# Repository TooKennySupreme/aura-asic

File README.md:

aura-asic
=========

## **Aura ASIC universal PCB | Created by the Community**

This project originated from the works of Jasinlee, and his universal PCB for most current and upcoming ASIC designs.

To see where this project started of from, please follow this link:- [Roots](https://litecointalk.org/index.php?topic=12567.0)

If you are waiting for the release of a scrypt ASIC, follow Jasinlee's project on [Litecointalk.org](https://litecointalk.org/index.php?topic=2702.0)

### To do list:
  - Convert board from Kicad to Altium
  - Convert board from Kicad to Eagle
  - TBUpdateded

### Current Issues:
  - item will be updated

### Contributors:

_jasinlee_:
LTCasicYDKQVGySmG5vwCiqiZFpMcr7oMi

_losh11_:
LfVszG74eZKRxrx2s29rQs3MR2Vvau3LsE

_smartbitcoin_: TBUpdateded

_artilectinc.com_: TBUpdateded

_Cheshyr_:
1CheshyrZsZ5X1XWW5EQUhGTExx6LTQBw4

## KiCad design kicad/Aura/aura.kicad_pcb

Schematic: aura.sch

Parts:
C1: 50p
C2, C23, C24, C25, C26: 22n
C3: 1.2n
C4: 1p
C5: .22u
C6: .1u
C7, C14, C15: 330u
C8, C9, C10, C11: 330n
C12: 10u
C13, C16, C17, C18, C19, C32, C33, C34, C35, C39, C40, C41, C42, C43, C44, C45, C46, C47, C48, C49, C50, C51, C52, C53, C54, C55, C56, C57, C58, C59, C60, C61, C62, C63, C64, C65, C66, C67, C68, C69, C70, C71, C72, C73, C74, C75, C76, C77, C78, C79, C80, C81, C82, C83, C84, C85, C86, C87, C88, C89, C90, C91, C92, C93, C94, C103, C104, C105, C106, C107, C108, C109, C110, C111, C112, C113, C114, C115, C116, C117, C118, C119, C120, C121, C122, C123, C124, C125, C126, C127, C128, C129, C130, C131, C132, C133, C134, C135, C136, C137, C138, C139, C140, C141, C142, C143, C144, C145, C146, C147, C148, C149, C150, C151, C152, C153, C154, C155, C156, C157, C158, C159, C160, C161, C162, C171, C172, C173, C174, C175, C176, C177, C178, C179, C180, C181, C182, C183, C184, C185, C186, C187, C188, C189, C190, C191, C192, C193, C194, C195, C196, C197, C198, C199, C200, C201, C202, C203, C204, C205, C206, C207, C208, C209, C210, C211, C212, C213, C214, C215, C216, C217, C218, C219, C220, C221, C222, C223, C224, C225, C226, C227, C228, C229, C230, C239, C240, C241, C242, C243, C244, C245, C246, C247, C248, C249, C250, C251, C252, C253, C254, C255, C256, C257, C258, C259, C260, C261, C262, C263, C264, C265, C266, C267, C268, C269, C270, C271, C272, C273, C274, C275, C276, C277, C278, C279, C280, C281, C282, C283, C284, C285, C286, C287, C288, C289, C290, C291, C292, C293, C294, C295, C296, C297, C298: 1u
C20: 10n
C21: 10nf
C22: 560u
C27, C28, C29, C30, C95, C96, C97, C98, C163, C164, C165, C166, C231, C232, C233, C234: 0.47u
C31, C36, C37, C38, C99, C100, C101, C102, C167, C168, C169, C170, C235, C236, C237, C238, C299: 0.1u
D1: VRRM = 45V
FB1, FB2, FB3: 120R
J1: PCIE_PWR
J2: USB
J3: DIL8
J4: DIL6
JP1, JP2, JP3, JP4: JUMPER
L1: 2.2u
L2, L3, L4, L5: 600n
Q1: FDG1024NZ; SC70-6
Q2, Q3, Q4, Q5, Q6, Q7, Q8, Q9: MOS_N
R1: 22k
R2: 19.1k
R3, R4, R5, R6, R9, R11, R17, R18, R32, R33, R34, R35, R36, R37, R38, R39, R44, R45, R46, R47, R48, R49, R50, R51, R56, R57, R58, R59, R60, R61, R62, R63, R68, R69, R70, R71, R72, R73, R74, R75: 1k
R7: 1G
R8: 100k
R10: 88k
R12: 11k
R13, R14, R15, R16: 8.4k
R19, R20, R26, R27, R28, R30, R41, R43, R53, R55, R65, R67: 10k
R21: 402
R22, R23, R24, R25: 27.3k
R29, R31, R40, R42, R52, R54, R64, R66: 5.6k
RP1: 10k
TH1: 6.8k RT
TH2, TH3: 2.2k RT
TP1, TP2, TP3, TP4, TP5, TP6, TP7, TP8, TP9, TP10, TP11, TP12, TP13, TP14, TP15: TST
U1: ISL6306
U2: PCF8574_SO16
U3: PCF8574_SO16
U4: LM340S
U5, U6, U7, U8: ISL6612
U9: LM22678
U11: 74LS138
U12: PIC16LF1459_SSOP20
U13, U14, U15, U16, U17, U18, U19, U20, U21, U22, U23, U24, U25, U26, U27, U28: ASIC

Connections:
+1.2V: C23.2, C24.2, C25.2, C26.2, C32.2, C33.2, C34.2, C35.2, C39.2, C40.2, C41.2, C42.2, C43.2, C44.2, C45.2, C46.2, C47.2, C48.2, C49.2, C50.2, C51.2, C52.2, C53.2, C54.2, C55.2, C56.2, C57.2, C58.2, C59.2, C60.2, C61.2, C62.2, C63.2, C64.2, C65.2, C66.2, C67.2, C68.2, C69.2, C70.2, C71.2, C72.2, C73.2, C74.2, C75.2, C76.2, C77.2, C78.2, C79.2, C80.2, C81.2, C82.2, C83.2, C84.2, C85.2, C86.2, C87.2, C88.2, C89.2, C90.2, C91.2, C92.2, C93.2, C94.2, C103.2, C104.2, C105.2, C106.2, C107.2, C108.2, C109.2, C110.2, C111.2, C112.2, C113.2, C114.2, C115.2, C116.2, C117.2, C118.2, C119.2, C120.2, C121.2, C122.2, C123.2, C124.2, C125.2, C126.2, C127.2, C128.2, C129.2, C130.2, C131.2, C132.2, C133.2, C134.2, C135.2, C136.2, C137.2, C138.2, C139.2, C140.2, C141.2, C142.2, C143.2, C144.2, C145.2, C146.2, C147.2, C148.2, C149.2, C150.2, C151.2, C152.2, C153.2, C154.2, C155.2, C156.2, C157.2, C158.2, C159.2, C160.2, C161.2, C162.2, C171.2, C172.2, C173.2, C174.2, C175.2, C176.2, C177.2, C178.2, C179.2, C180.2, C181.2, C182.2, C183.2, C184.2, C185.2, C186.2, C187.2, C188.2, C189.2, C190.2, C191.2, C192.2, C193.2, C194.2, C195.2, C196.2, C197.2, C198.2, C199.2, C200.2, C201.2, C202.2, C203.2, C204.2, C205.2, C206.2, C207.2, C208.2, C209.2, C210.2, C211.2, C212.2, C213.2, C214.2, C215.2, C216.2, C217.2, C218.2, C219.2, C220.2, C221.2, C222.2, C223.2, C224.2, C225.2, C226.2, C227.2, C228.2, C229.2, C230.2, C239.2, C240.2, C241.2, C242.2, C243.2, C244.2, C245.2, C246.2, C247.2, C248.2, C249.2, C250.2, C251.2, C252.2, C253.2, C254.2, C255.2, C256.2, C257.2, C258.2, C259.2, C260.2, C261.2, C262.2, C263.2, C264.2, C265.2, C266.2, C267.2, C268.2, C269.2, C270.2, C271.2, C272.2, C273.2, C274.2, C275.2, C276.2, C277.2, C278.2, C279.2, C280.2, C281.2, C282.2, C283.2, C284.2, C285.2, C286.2, C287.2, C288.2, C289.2, C290.2, C291.2, C292.2, C293.2, C294.2, C295.2, C296.2, C297.2, C298.2, L2.2, L3.2, L4.2, L5.2, R13.2, R14.1, R15.2, R16.2, TP13.1, U1.17 (VSEN), U13.14 (VDD), U13.15 (VDD), U13.16 (VDD), U13.17 (VDD), U13.18 (VDD), U13.19 (VDD), U13.20 (VDD), U13.21 (VDD), U13.22 (VDD), U13.23 (VDD), U13.24 (VDD), U13.25 (VDD), U13.26 (VDD), U13.27 (VDD), U13.28 (VDD), U13.29 (VDD), U13.30 (VDD), U13.31 (VDD), U13.32 (VDD), U13.33 (VDD), U13.34 (VDD), U13.35 (VDD), U13.36 (VDD), U13.37 (VDD), U13.38 (VDD), U13.39 (VDD), U13.40 (VDD), U13.41 (VDD), U13.42 (VDD), U13.43 (VDD), U13.44 (VDD), U13.45 (VDD), U13.46 (VDD), U13.47 (VDD), U13.48 (VDD), U14.14 (VDD), U14.15 (VDD), U14.16 (VDD), U14.17 (VDD), U14.18 (VDD), U14.19 (VDD), U14.20 (VDD), U14.21 (VDD), U14.22 (VDD), U14.23 (VDD), U14.24 (VDD), U14.25 (VDD), U14.26 (VDD), U14.27 (VDD), U14.28 (VDD), U14.29 (VDD), U14.30 (VDD), U14.31 (VDD), U14.32 (VDD), U14.33 (VDD), U14.34 (VDD), U14.35 (VDD), U14.36 (VDD), U14.37 (VDD), U14.38 (VDD), U14.39 (VDD), U14.40 (VDD), U14.41 (VDD), U14.42 (VDD), U14.43 (VDD), U14.44 (VDD), U14.45 (VDD), U14.46 (VDD), U14.47 (VDD), U14.48 (VDD), U15.14 (VDD), U15.15 (VDD), U15.16 (VDD), U15.17 (VDD), U15.18 (VDD), U15.19 (VDD), U15.20 (VDD), U15.21 (VDD), U15.22 (VDD), U15.23 (VDD), U15.24 (VDD), U15.25 (VDD), U15.26 (VDD), U15.27 (VDD), U15.28 (VDD), U15.29 (VDD), U15.30 (VDD), U15.31 (VDD), U15.32 (VDD), U15.33 (VDD), U15.34 (VDD), U15.35 (VDD), U15.36 (VDD), U15.37 (VDD), U15.38 (VDD), U15.39 (VDD), U15.40 (VDD), U15.41 (VDD), U15.42 (VDD), U15.43 (VDD), U15.44 (VDD), U15.45 (VDD), U15.46 (VDD), U15.47 (VDD), U15.48 (VDD), U16.14 (VDD), U16.15 (VDD), U16.16 (VDD), U16.17 (VDD), U16.18 (VDD), U16.19 (VDD), U16.20 (VDD), U16.21 (VDD), U16.22 (VDD), U16.23 (VDD), U16.24 (VDD), U16.25 (VDD), U16.26 (VDD), U16.27 (VDD), U16.28 (VDD), U16.29 (VDD), U16.30 (VDD), U16.31 (VDD), U16.32 (VDD), U16.33 (VDD), U16.34 (VDD), U16.35 (VDD), U16.36 (VDD), U16.37 (VDD), U16.38 (VDD), U16.39 (VDD), U16.40 (VDD), U16.41 (VDD), U16.42 (VDD), U16.43 (VDD), U16.44 (VDD), U16.45 (VDD), U16.46 (VDD), U16.47 (VDD), U16.48 (VDD), U17.14 (VDD), U17.15 (VDD), U17.16 (VDD), U17.17 (VDD), U17.18 (VDD), U17.19 (VDD), U17.20 (VDD), U17.21 (VDD), U17.22 (VDD), U17.23 (VDD), U17.24 (VDD), U17.25 (VDD), U17.26 (VDD), U17.27 (VDD), U17.28 (VDD), U17.29 (VDD), U17.30 (VDD), U17.31 (VDD), U17.32 (VDD), U17.33 (VDD), U17.34 (VDD), U17.35 (VDD), U17.36 (VDD), U17.37 (VDD), U17.38 (VDD), U17.39 (VDD), U17.40 (VDD), U17.41 (VDD), U17.42 (VDD), U17.43 (VDD), U17.44 (VDD), U17.45 (VDD), U17.46 (VDD), U17.47 (VDD), U17.48 (VDD), U18.14 (VDD), U18.15 (VDD), U18.16 (VDD), U18.17 (VDD), U18.18 (VDD), U18.19 (VDD), U18.20 (VDD), U18.21 (VDD), U18.22 (VDD), U18.23 (VDD), U18.24 (VDD), U18.25 (VDD), U18.26 (VDD), U18.27 (VDD), U18.28 (VDD), U18.29 (VDD), U18.30 (VDD), U18.31 (VDD), U18.32 (VDD), U18.33 (VDD), U18.34 (VDD), U18.35 (VDD), U18.36 (VDD), U18.37 (VDD), U18.38 (VDD), U18.39 (VDD), U18.40 (VDD), U18.41 (VDD), U18.42 (VDD), U18.43 (VDD), U18.44 (VDD), U18.45 (VDD), U18.46 (VDD), U18.47 (VDD), U18.48 (VDD), U19.14 (VDD), U19.15 (VDD), U19.16 (VDD), U19.17 (VDD), U19.18 (VDD), U19.19 (VDD), U19.20 (VDD), U19.21 (VDD), U19.22 (VDD), U19.23 (VDD), U19.24 (VDD), U19.25 (VDD), U19.26 (VDD), U19.27 (VDD), U19.28 (VDD), U19.29 (VDD), U19.30 (VDD), U19.31 (VDD), U19.32 (VDD), U19.33 (VDD), U19.34 (VDD), U19.35 (VDD), U19.36 (VDD), U19.37 (VDD), U19.38 (VDD), U19.39 (VDD), U19.40 (VDD), U19.41 (VDD), U19.42 (VDD), U19.43 (VDD), U19.44 (VDD), U19.45 (VDD), U19.46 (VDD), U19.47 (VDD), U19.48 (VDD), U20.14 (VDD), U20.15 (VDD), U20.16 (VDD), U20.17 (VDD), U20.18 (VDD), U20.19 (VDD), U20.20 (VDD), U20.21 (VDD), U20.22 (VDD), U20.23 (VDD), U20.24 (VDD), U20.25 (VDD), U20.26 (VDD), U20.27 (VDD), U20.28 (VDD), U20.29 (VDD), U20.30 (VDD), U20.31 (VDD), U20.32 (VDD), U20.33 (VDD), U20.34 (VDD), U20.35 (VDD), U20.36 (VDD), U20.37 (VDD), U20.38 (VDD), U20.39 (VDD), U20.40 (VDD), U20.41 (VDD), U20.42 (VDD), U20.43 (VDD), U20.44 (VDD), U20.45 (VDD), U20.46 (VDD), U20.47 (VDD), U20.48 (VDD), U21.14 (VDD), U21.15 (VDD), U21.16 (VDD), U21.17 (VDD), U21.18 (VDD), U21.19 (VDD), U21.20 (VDD), U21.21 (VDD), U21.22 (VDD), U21.23 (VDD), U21.24 (VDD), U21.25 (VDD), U21.26 (VDD), U21.27 (VDD), U21.28 (VDD), U21.29 (VDD), U21.30 (VDD), U21.31 (VDD), U21.32 (VDD), U21.33 (VDD), U21.34 (VDD), U21.35 (VDD), U21.36 (VDD), U21.37 (VDD), U21.38 (VDD), U21.39 (VDD), U21.40 (VDD), U21.41 (VDD), U21.42 (VDD), U21.43 (VDD), U21.44 (VDD), U21.45 (VDD), U21.46 (VDD), U21.47 (VDD), U21.48 (VDD), U22.14 (VDD), U22.15 (VDD), U22.16 (VDD), U22.17 (VDD), U22.18 (VDD), U22.19 (VDD), U22.20 (VDD), U22.21 (VDD), U22.22 (VDD), U22.23 (VDD), U22.24 (VDD), U22.25 (VDD), U22.26 (VDD), U22.27 (VDD), U22.28 (VDD), U22.29 (VDD), U22.30 (VDD), U22.31 (VDD), U22.32 (VDD), U22.33 (VDD), U22.34 (VDD), U22.35 (VDD), U22.36 (VDD), U22.37 (VDD), U22.38 (VDD), U22.39 (VDD), U22.40 (VDD), U22.41 (VDD), U22.42 (VDD), U22.43 (VDD), U22.44 (VDD), U22.45 (VDD), U22.46 (VDD), U22.47 (VDD), U22.48 (VDD), U23.14 (VDD), U23.15 (VDD), U23.16 (VDD), U23.17 (VDD), U23.18 (VDD), U23.19 (VDD), U23.20 (VDD), U23.21 (VDD), U23.22 (VDD), U23.23 (VDD), U23.24 (VDD), U23.25 (VDD), U23.26 (VDD), U23.27 (VDD), U23.28 (VDD), U23.29 (VDD), U23.30 (VDD), U23.31 (VDD), U23.32 (VDD), U23.33 (VDD), U23.34 (VDD), U23.35 (VDD), U23.36 (VDD), U23.37 (VDD), U23.38 (VDD), U23.39 (VDD), U23.40 (VDD), U23.41 (VDD), U23.42 (VDD), U23.43 (VDD), U23.44 (VDD), U23.45 (VDD), U23.46 (VDD), U23.47 (VDD), U23.48 (VDD), U24.14 (VDD), U24.15 (VDD), U24.16 (VDD), U24.17 (VDD), U24.18 (VDD), U24.19 (VDD), U24.20 (VDD), U24.21 (VDD), U24.22 (VDD), U24.23 (VDD), U24.24 (VDD), U24.25 (VDD), U24.26 (VDD), U24.27 (VDD), U24.28 (VDD), U24.29 (VDD), U24.30 (VDD), U24.31 (VDD), U24.32 (VDD), U24.33 (VDD), U24.34 (VDD), U24.35 (VDD), U24.36 (VDD), U24.37 (VDD), U24.38 (VDD), U24.39 (VDD), U24.40 (VDD), U24.41 (VDD), U24.42 (VDD), U24.43 (VDD), U24.44 (VDD), U24.45 (VDD), U24.46 (VDD), U24.47 (VDD), U24.48 (VDD), U25.14 (VDD), U25.15 (VDD), U25.16 (VDD), U25.17 (VDD), U25.18 (VDD), U25.19 (VDD), U25.20 (VDD), U25.21 (VDD), U25.22 (VDD), U25.23 (VDD), U25.24 (VDD), U25.25 (VDD), U25.26 (VDD), U25.27 (VDD), U25.28 (VDD), U25.29 (VDD), U25.30 (VDD), U25.31 (VDD), U25.32 (VDD), U25.33 (VDD), U25.34 (VDD), U25.35 (VDD), U25.36 (VDD), U25.37 (VDD), U25.38 (VDD), U25.39 (VDD), U25.40 (VDD), U25.41 (VDD), U25.42 (VDD), U25.43 (VDD), U25.44 (VDD), U25.45 (VDD), U25.46 (VDD), U25.47 (VDD), U25.48 (VDD), U26.14 (VDD), U26.15 (VDD), U26.16 (VDD), U26.17 (VDD), U26.18 (VDD), U26.19 (VDD), U26.20 (VDD), U26.21 (VDD), U26.22 (VDD), U26.23 (VDD), U26.24 (VDD), U26.25 (VDD), U26.26 (VDD), U26.27 (VDD), U26.28 (VDD), U26.29 (VDD), U26.30 (VDD), U26.31 (VDD), U26.32 (VDD), U26.33 (VDD), U26.34 (VDD), U26.35 (VDD), U26.36 (VDD), U26.37 (VDD), U26.38 (VDD), U26.39 (VDD), U26.40 (VDD), U26.41 (VDD), U26.42 (VDD), U26.43 (VDD), U26.44 (VDD), U26.45 (VDD), U26.46 (VDD), U26.47 (VDD), U26.48 (VDD), U27.14 (VDD), U27.15 (VDD), U27.16 (VDD), U27.17 (VDD), U27.18 (VDD), U27.19 (VDD), U27.20 (VDD), U27.21 (VDD), U27.22 (VDD), U27.23 (VDD), U27.24 (VDD), U27.25 (VDD), U27.26 (VDD), U27.27 (VDD), U27.28 (VDD), U27.29 (VDD), U27.30 (VDD), U27.31 (VDD), U27.32 (VDD), U27.33 (VDD), U27.34 (VDD), U27.35 (VDD), U27.36 (VDD), U27.37 (VDD), U27.38 (VDD), U27.39 (VDD), U27.40 (VDD), U27.41 (VDD), U27.42 (VDD), U27.43 (VDD), U27.44 (VDD), U27.45 (VDD), U27.46 (VDD), U27.47 (VDD), U27.48 (VDD), U28.14 (VDD), U28.15 (VDD), U28.16 (VDD), U28.17 (VDD), U28.18 (VDD), U28.19 (VDD), U28.20 (VDD), U28.21 (VDD), U28.22 (VDD), U28.23 (VDD), U28.24 (VDD), U28.25 (VDD), U28.26 (VDD), U28.27 (VDD), U28.28 (VDD), U28.29 (VDD), U28.30 (VDD), U28.31 (VDD), U28.32 (VDD), U28.33 (VDD), U28.34 (VDD), U28.35 (VDD), U28.36 (VDD), U28.37 (VDD), U28.38 (VDD), U28.39 (VDD), U28.40 (VDD), U28.41 (VDD), U28.42 (VDD), U28.43 (VDD), U28.44 (VDD), U28.45 (VDD), U28.46 (VDD), U28.47 (VDD), U28.48 (VDD)
+1.8V: C22.1, C27.1, C28.1, C29.1, C30.1, C95.1, C96.1, C97.1, C98.1, C163.1, C164.1, C165.1, C166.1, C231.1, C232.1, C233.1, C234.1, L1.2, R21.2, R32.1, R34.1, R35.1, R36.1, R44.1, R45.1, R46.1, R47.1, R56.1, R57.1, R58.1, R59.1, R68.1, R69.1, R70.1, R71.1, TP8.1, U13.4 (IOVDD), U14.4 (IOVDD), U15.4 (IOVDD), U16.4 (IOVDD), U17.4 (IOVDD), U18.4 (IOVDD), U19.4 (IOVDD), U20.4 (IOVDD), U21.4 (IOVDD), U22.4 (IOVDD), U23.4 (IOVDD), U24.4 (IOVDD), U25.4 (IOVDD), U26.4 (IOVDD), U27.4 (IOVDD), U28.4 (IOVDD)
+5V: C6.1, J3.3, J4.5, R4.2, R5.2, R9.2, R17.2, R19.1, R20.1, R26.1, R27.1, RP1.1, RP1.2, RP1.3, RP1.4, RP1.5, RP1.6, RP1.7, RP1.8, TP2.1, U1.8 (VRSEL), U1.19 (VCC), U2.1 (A0), U2.2 (A1), U2.3 (A2), U2.16 (VDD), U3.16 (VDD), U4.3 (OUT), U9.7 (EN), U12.1 (VDD)
+12V: C5.1, C7.1, C12.1, C13.1, C14.1, C15.1, C16.1, C17.1, C18.1, C19.1, J1.1, J1.2, J1.3, J3.7, Q2.D, Q4.D, Q6.D, Q8.D, R12.2, TP1.1, U4.1 (IN), U5.6 (VCC), U5.7 (PVCC), U6.6 (VCC), U6.7 (PVCC), U7.6 (VCC), U7.7 (PVCC), U8.6 (VCC), U8.7 (PVCC), U9.2 (VIN)
GND: C2.2, C5.2, C6.2, C7.2, C12.2, C13.2, C14.2, C15.2, C16.2, C17.2, C18.2, C19.2, C21.2, C22.2, C27.2, C28.2, C29.2, C30.2, C31.1, C32.1, C33.1, C34.1, C35.1, C36.1, C37.1, C38.1, C39.1, C40.1, C41.1, C42.1, C43.1, C44.1, C45.1, C46.1, C47.1, C48.1, C49.1, C50.1, C51.1, C52.1, C53.1, C54.1, C55.1, C56.1, C57.1, C58.1, C59.1, C60.1, C61.1, C62.1, C63.1, C64.1, C65.1, C66.1, C67.1, C68.1, C69.1, C70.1, C71.1, C72.1, C73.1, C74.1, C75.1, C76.1, C77.1, C78.1, C79.1, C80.1, C81.1, C82.1, C83.1, C84.1, C85.1, C86.1, C87.1, C88.1, C89.1, C90.1, C91.1, C92.1, C93.1, C94.1, C95.2, C96.2, C97.2, C98.2, C99.1, C100.1, C101.1, C102.1, C103.1, C104.1, C105.1, C106.1, C107.1, C108.1, C109.1, C110.1, C111.1, C112.1, C113.1, C114.1, C115.1, C116.1, C117.1, C118.1, C119.1, C120.1, C121.1, C122.1, C123.1, C124.1, C125.1, C126.1, C127.1, C128.1, C129.1, C130.1, C131.1, C132.1, C133.1, C134.1, C135.1, C136.1, C137.1, C138.1, C139.1, C140.1, C141.1, C142.1, C143.1, C144.1, C145.1, C146.1, C147.1, C148.1, C149.1, C150.1, C151.1, C152.1, C153.1, C154.1, C155.1, C156.1, C157.1, C158.1, C159.1, C160.1, C161.1, C162.1, C163.2, C164.2, C165.2, C166.2, C167.1, C168.1, C169.1, C170.1, C171.1, C172.1, C173.1, C174.1, C175.1, C176.1, C177.1, C178.1, C179.1, C180.1, C181.1, C182.1, C183.1, C184.1, C185.1, C186.1, C187.1, C188.1, C189.1, C190.1, C191.1, C192.1, C193.1, C194.1, C195.1, C196.1, C197.1, C198.1, C199.1, C200.1, C201.1, C202.1, C203.1, C204.1, C205.1, C206.1, C207.1, C208.1, C209.1, C210.1, C211.1, C212.1, C213.1, C214.1, C215.1, C216.1, C217.1, C218.1, C219.1, C220.1, C221.1, C222.1, C223.1, C224.1, C225.1, C226.1, C227.1, C228.1, C229.1, C230.1, C231.2, C232.2, C233.2, C234.2, C235.1, C236.1, C237.1, C238.1, C239.1, C240.1, C241.1, C242.1, C243.1, C244.1, C245.1, C246.1, C247.1, C248.1, C249.1, C250.1, C251.1, C252.1, C253.1, C254.1, C255.1, C256.1, C257.1, C258.1, C259.1, C260.1, C261.1, C262.1, C263.1, C264.1, C265.1, C266.1, C267.1, C268.1, C269.1, C270.1, C271.1, C272.1, C273.1, C274.1, C275.1, C276.1, C277.1, C278.1, C279.1, C280.1, C281.1, C282.1, C283.1, C284.1, C285.1, C286.1, C287.1, C288.1, C289.1, C290.1, C291.1, C292.1, C293.1, C294.1, C295.1, C296.1, C297.1, C298.1, C299.2, D1.1 (A), FB1.1, FB2.1, FB3.1, J1.4, J1.5, J1.6, J3.1, J3.2, J4.6, JP1.2, JP2.2, JP3.2, JP4.2, Q1.1 (S), Q3.S, Q5.S, Q7.S, Q9.S, R1.2, R6.1, R8.1, R10.1, R18.2, R29.2, R31.2, R33.1, R37.1, R38.1, R39.1, R40.1, R42.1, R48.1, R49.1, R50.1, R51.1, R52.1, R54.1, R60.1, R61.1, R62.1, R63.1, R64.1, R66.1, R72.1, R73.1, R74.1, R75.1, TH1.1, TH2.2, TH3.2, U1.0 (GND), U1.16 (RGND), U1.18 (TCOMP), U2.8 (VSS), U3.1 (A0), U3.2 (A1), U3.3 (A2), U3.8 (VSS), U3.13 (INT_N), U4.2 (GND), U5.4 (GND), U6.4 (GND), U7.4 (GND), U8.4 (GND), U9.0 (GND), U9.4 (GND), U9.5 (NC), U11.3 (A2), U11.4 (E1), U11.5 (E2), U11.7 (O7), U11.8 (GND), U11.9 (O6), U11.10 (O5), U11.11 (O4), U12.20 (VSS), U13.1 (CMQ), U13.2 (CM_P), U13.3 (CM_N), U13.49 (GND), U14.1 (CMQ), U14.2 (CM_P), U14.3 (CM_N), U14.5 (OUTCLK), U14.6 (OUTSCK), U14.7 (OUTMOSI), U14.8 (OUTMISO), U14.49 (GND), U15.1 (CMQ), U15.2 (CM_P), U15.3 (CM_N), U15.49 (GND), U16.1 (CMQ), U16.2 (CM_P), U16.3 (CM_N), U16.49 (GND), U17.1 (CMQ), U17.2 (CM_P), U17.3 (CM_N), U17.5 (OUTCLK), U17.6 (OUTSCK), U17.7 (OUTMOSI), U17.8 (OUTMISO), U17.49 (GND), U18.1 (CMQ), U18.2 (CM_P), U18.3 (CM_N), U18.49 (GND), U19.1 (CMQ), U19.2 (CM_P), U19.3 (CM_N), U19.49 (GND), U20.1 (CMQ), U20.2 (CM_P), U20.3 (CM_N), U20.49 (GND), U21.1 (CMQ), U21.2 (CM_P), U21.3 (CM_N), U21.5 (OUTCLK), U21.6 (OUTSCK), U21.7 (OUTMOSI), U21.8 (OUTMISO), U21.49 (GND), U22.1 (CMQ), U22.2 (CM_P), U22.3 (CM_N), U22.49 (GND), U23.1 (CMQ), U23.2 (CM_P), U23.3 (CM_N), U23.49 (GND), U24.1 (CMQ), U24.2 (CM_P), U24.3 (CM_N), U24.49 (GND), U25.1 (CMQ), U25.2 (CM_P), U25.3 (CM_N), U25.5 (OUTCLK), U25.6 (OUTSCK), U25.7 (OUTMOSI), U25.8 (OUTMISO), U25.49 (GND), U26.1 (CMQ), U26.2 (CM_P), U26.3 (CM_N), U26.49 (GND), U27.1 (CMQ), U27.2 (CM_P), U27.3 (CM_N), U27.49 (GND), U28.1 (CMQ), U28.2 (CM_P), U28.3 (CM_N), U28.49 (GND)
unnamed: U15.11 (INSCK), U16.6 (OUTSCK)
unnamed: U13.7 (OUTMOSI), U16.10 (INMOSI)
unnamed: U13.8 (OUTMISO), U16.9 (INMISO)
unnamed: U15.12 (INCLK), U16.5 (OUTCLK)
unnamed: U15.10 (INMOSI), U16.7 (OUTMOSI)
unnamed: U15.9 (INMISO), U16.8 (OUTMISO)
unnamed: U14.12 (INCLK), U15.5 (OUTCLK)
unnamed: U13.5 (OUTCLK), U16.12 (INCLK)
unnamed: U13.6 (OUTSCK), U16.11 (INSCK)
unnamed: U19.10 (INMOSI), U20.7 (OUTMOSI)
unnamed: U19.9 (INMISO), U20.8 (OUTMISO)
unnamed: U18.12 (INCLK), U19.5 (OUTCLK)
unnamed: U18.11 (INSCK), U19.6 (OUTSCK)
unnamed: U18.10 (INMOSI), U19.7 (OUTMOSI)
unnamed: U18.9 (INMISO), U19.8 (OUTMISO)
unnamed: U17.12 (INCLK), U18.5 (OUTCLK)
unnamed: U14.9 (INMISO), U15.8 (OUTMISO)
unnamed: U14.11 (INSCK), U15.6 (OUTSCK)
unnamed: U14.10 (INMOSI), U15.7 (OUTMOSI)
unnamed: U19.12 (INCLK), U20.5 (OUTCLK)
unnamed: U19.11 (INSCK), U20.6 (OUTSCK)
unnamed: U17.11 (INSCK), U18.6 (OUTSCK)
unnamed: C102.2, R47.2, R51.2, U20.13 (IOREF)
unnamed: C167.2, R56.2, R60.2, U21.13 (IOREF)
unnamed: U17.10 (INMOSI), U18.7 (OUTMOSI)
unnamed: U17.9 (INMISO), U18.8 (OUTMISO)
unnamed: C101.2, R46.2, R50.2, U19.13 (IOREF)
unnamed: C37.2, R35.2, R38.2, U15.13 (IOREF)
unnamed: C38.2, R36.2, R39.2, U16.13 (IOREF)
unnamed: C235.2, R68.2, R72.2, U25.13 (IOREF)
unnamed: U21.11 (INSCK), U22.6 (OUTSCK)
unnamed: U22.10 (INMOSI), U23.7 (OUTMOSI)
unnamed: U22.9 (INMISO), U23.8 (OUTMISO)
unnamed: U21.12 (INCLK), U22.5 (OUTCLK)
unnamed: U21.10 (INMOSI), U22.7 (OUTMOSI)
unnamed: U21.9 (INMISO), U22.8 (OUTMISO)
unnamed: C237.2, R70.2, R74.2, U27.13 (IOREF)
unnamed: C236.2, R69.2, R73.2, U26.13 (IOREF)
unnamed: C169.2, R58.2, R62.2, U23.13 (IOREF)
unnamed: C168.2, R57.2, R61.2, U22.13 (IOREF)
unnamed: C170.2, R59.2, R63.2, U24.13 (IOREF)
unnamed: U23.12 (INCLK), U24.5 (OUTCLK)
unnamed: U23.11 (INSCK), U24.6 (OUTSCK)
unnamed: U23.10 (INMOSI), U24.7 (OUTMOSI)
unnamed: U23.9 (INMISO), U24.8 (OUTMISO)
unnamed: U22.12 (INCLK), U23.5 (OUTCLK)
unnamed: U22.11 (INSCK), U23.6 (OUTSCK)
unnamed: U1.20 (PWM1), U8.3 (PWM)
unnamed: U1.31 (PWM3), U5.3 (PWM)
unnamed: Q7.G, U7.5 (LGATE)
unnamed: R4.1, TH2.1, U12.7 (RC3)
unnamed: U1.25 (PWM4), U7.3 (PWM)
unnamed: U1.26 (PWM2), U6.3 (PWM)
unnamed: Q1.2 (G), U12.10 (RB7)
unnamed: J4.3, U12.4 (RA3)
unnamed: R66.2, R67.1, U28.11 (INSCK)
unnamed: R64.2, R65.1, U28.10 (INMOSI)
unnamed: C9.1, L5.1, Q8.S, Q9.D, R25.1, U8.8 (PHASE)
unnamed: Q8.G, U8.1 (UGATE)
unnamed: C8.1, L4.1, Q6.S, Q7.D, R24.1, U7.8 (PHASE)
unnamed: C10.2, U5.2 (BOOT)
unnamed: Q9.G, U8.5 (LGATE)
unnamed: Q5.G, U6.5 (LGATE)
unnamed: Q3.G, U5.5 (LGATE)
unnamed: Q2.G, U5.1 (UGATE)
unnamed: Q4.G, U6.1 (UGATE)
unnamed: Q6.G, U7.1 (UGATE)
unnamed: C11.2, U6.2 (BOOT)
unnamed: C11.1, L3.1, Q4.S, Q5.D, R23.1, U6.8 (PHASE)
unnamed: C10.1, L2.1, Q2.S, Q3.D, R22.1, U5.8 (PHASE)
unnamed: C8.2, U7.2 (BOOT)
unnamed: R55.2, TP11.1, U11.13 (O2)
unnamed: FB3.2, J2.5 (Shield_1)
unnamed: FB2.2, J2.6 (Shield_2)
unnamed: FB1.2, J2.4 (GND)
unnamed: R28.1, TP9.1, U11.15 (O0)
unnamed: R67.2, TP12.1, U11.12 (O3)
unnamed: R43.2, TP10.1, U11.14 (O1)
unnamed: J2.3 (D+), TP7.1, U12.19 (RA0)
unnamed: J2.2 (D-), TP4.1, U12.18 (RA1)
unnamed: R9.1, TH3.1, U12.8 (RC6)
unnamed: TP6.1, U11.6 (E3), U12.6 (RC4)
unnamed: JP4.1, U28.12 (INCLK)
unnamed: JP3.1, U24.12 (INCLK)
unnamed: JP2.1, U20.12 (INCLK)
unnamed: TP3.1, U11.1 (A0), U12.2 (RA5)
unnamed: C36.2, R34.2, R37.2, U14.13 (IOREF)
unnamed: C99.2, R44.2, R48.2, U17.13 (IOREF)
unnamed: C100.2, R45.2, R49.2, U18.13 (IOREF)
unnamed: R6.2, R12.1, U1.32 (EN_PWR)
unnamed: R10.2, U1.34 (FS)
unnamed: U1.36 (VR_RDY), U2.6 (P2)
unnamed: R1.1, U1.9 (OFS)
unnamed: C2.1, R3.2, U1.11 (REF)
unnamed: R3.1, U1.10 (DAC)
unnamed: C24.1, R23.2, U1.28 (ISEN2-)
unnamed: C23.1, R22.2, U1.29 (ISEN3-)
unnamed: R15.1, U1.27 (ISEN2+)
unnamed: R8.2, U1.35 (SS)
unnamed: C25.1, R24.2, U1.23 (ISEN4-)
unnamed: R16.1, U1.24 (ISEN4+)
unnamed: C9.2, U8.2 (BOOT)
unnamed: C26.1, R25.2, U1.22 (ISEN1-)
unnamed: R13.1, U1.21 (ISEN1+)
unnamed: J3.4, R20.2, U12.13 (RB4)
unnamed: J3.5, R19.2, U12.11 (RB6)
unnamed: J3.6, R17.1
unnamed: J4.2, U12.16 (RC0)
unnamed: J4.1, U12.15 (RC1)
unnamed: R30.2, R31.1, R41.2, R53.2, R65.2, TP14.1, U13.10 (INMOSI)
unnamed: R28.2, R29.1, U13.11 (INSCK)
unnamed: C31.2, R32.2, R33.2, U13.13 (IOREF)
unnamed: J3.8, Q1.6 (D)
unnamed: C299.1, U12.17 (Vusb)
unnamed: R30.1, U12.5 (RC5)
unnamed: R42.2, R43.1, U20.11 (INSCK)
unnamed: R40.2, R41.1, U20.10 (INMOSI)
unnamed: R14.2, U1.30 (ISEN3+)
unnamed: C1.2, C3.2, C4.2, R11.2, U1.13 (FB), U1.14 (IDROOP)
unnamed: C3.1, R2.2
unnamed: C1.1, R2.1, U1.12 (COMP)
unnamed: C4.1, R7.2
unnamed: R5.1, TH1.2, U1.39 (TM)
unnamed: U1.38 (VR_HOT), U2.4 (P0)
unnamed: RP1.9 (R8), U1.40 (VID7), U3.12 (P7)
unnamed: R7.1, R11.1, U1.15 (VDIFF)
unnamed: U1.33 (EN_VTT), U2.7 (P3)
unnamed: JP1.1, U13.12 (INCLK)
unnamed: U1.37 (VR_FAN), U2.5 (P1)
unnamed: R54.2, R55.1, U24.11 (INSCK)
unnamed: C20.1, U9.3 (BOOT)
unnamed: C20.2, D1.2 (K), L1.1, U9.1 (SW)
unnamed: R18.1, R21.1, U9.6 (FB)
unnamed: TP5.1, U11.2 (A1), U12.3 (RA4)
unnamed: TP15.1, U12.9 (RC7), U13.9 (INMISO), U20.9 (INMISO), U24.9 (INMISO), U28.9 (INMISO)
unnamed: R52.2, R53.1, U24.10 (INMOSI)
unnamed: C238.2, R71.2, R75.2, U28.13 (IOREF)
unnamed: U27.12 (INCLK), U28.5 (OUTCLK)
unnamed: U27.11 (INSCK), U28.6 (OUTSCK)
unnamed: U27.10 (INMOSI), U28.7 (OUTMOSI)
unnamed: RP1.15 (R2), U1.6 (VID1), U3.5 (P1)
unnamed: RP1.14 (R3), U1.5 (VID2), U3.6 (P2)
unnamed: RP1.13 (R4), U1.4 (VID3), U3.7 (P3)
unnamed: RP1.12 (R5), U1.3 (VID4), U3.9 (P4)
unnamed: RP1.11 (R6), U1.2 (VID5), U3.10 (P5)
unnamed: RP1.10 (R7), U1.1 (VID6), U3.11 (P6)
unnamed: RP1.16 (R1), U1.7 (VID0), U3.4 (P0)
unnamed: R26.2, U2.14 (SCL), U3.14 (SCL), U12.12 (RB5)
unnamed: R27.2, U2.15 (SDA), U3.15 (SDA), U12.14 (RC2)
unnamed: U25.11 (INSCK), U26.6 (OUTSCK)
unnamed: U25.12 (INCLK), U26.5 (OUTCLK)
unnamed: U25.10 (INMOSI), U26.7 (OUTMOSI)
unnamed: U25.9 (INMISO), U26.8 (OUTMISO)
unnamed: U27.9 (INMISO), U28.8 (OUTMISO)
unnamed: U26.12 (INCLK), U27.5 (OUTCLK)
unnamed: U26.11 (INSCK), U27.6 (OUTSCK)
unnamed: U26.10 (INMOSI), U27.7 (OUTMOSI)
unnamed: U26.9 (INMISO), U27.8 (OUTMISO)

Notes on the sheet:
RA3 - MCLR RC1 - ICSP_CLK RC0 - ICSP_DAT
ICSP
FAN
I2C
Board seems to be good enough at least for lower-power test! We placed 15 1uF murata capacitors. We placed also 10 uF kemet capacitors where tantalum capacitors were expected and into input vdd we placed 1000 uF electrolytic cap. Connected this to lab power supply. Should be good enough. <- from bi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

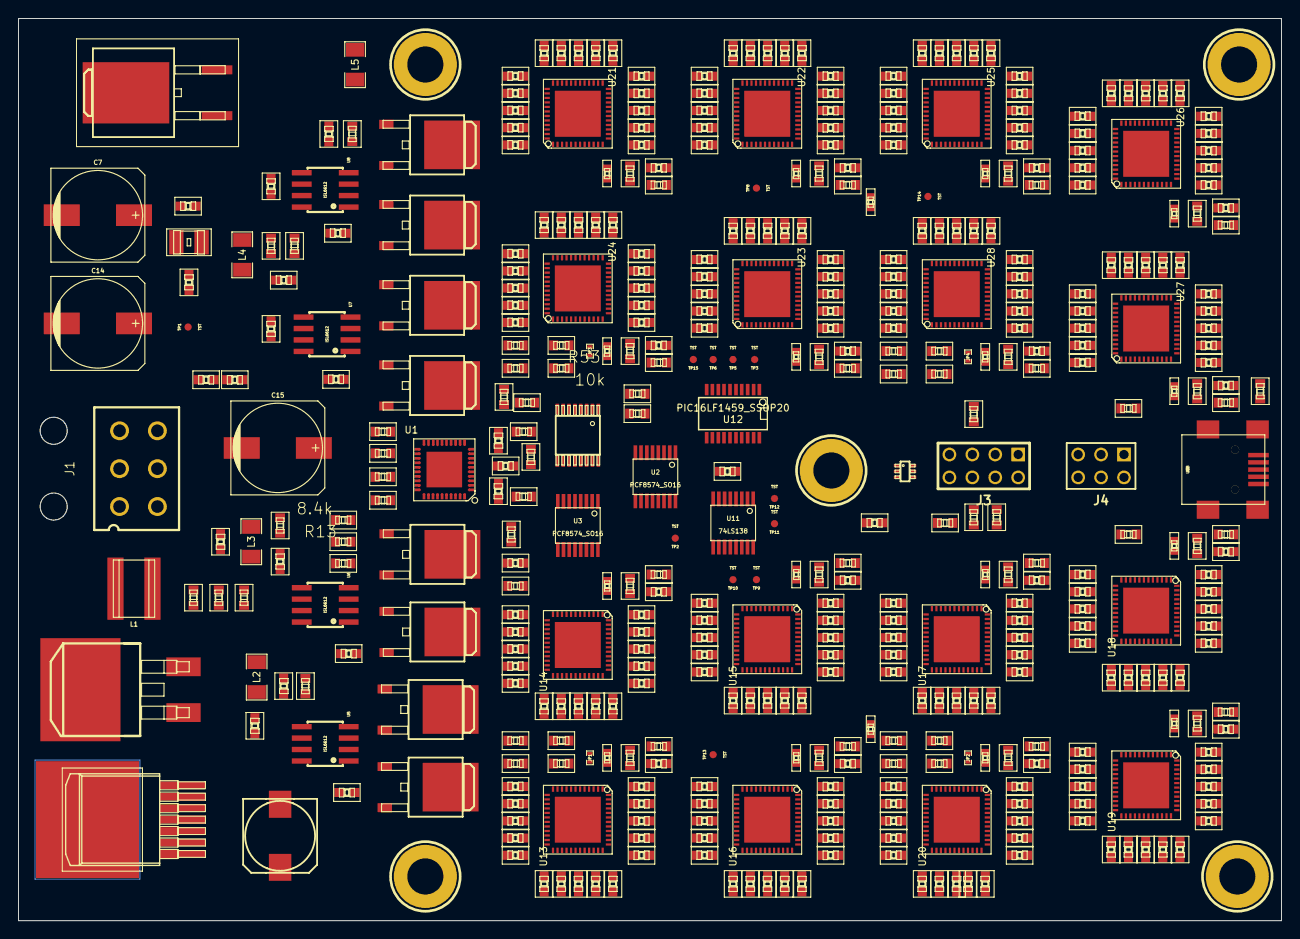
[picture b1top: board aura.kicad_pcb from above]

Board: 4 copper layers, 140.0 x 100.0 mm, 449 parts (0 on the bottom side), 163 nets, no tracks yet.

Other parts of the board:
P1, P2, P3, P4, P5: Hole4mm

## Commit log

2014-01-09 Added
2014-01-10 Formatted.
2014-01-10 Fixed format.
2014-01-10 Added more info and links.
2014-01-10 Corrected the spelling of scrypt and removed unused whitespace
